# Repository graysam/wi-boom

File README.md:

# PeRci (ESP32 / ESP32-S3)

Firmware for ESP32 boards hosting a minimal web UI to safely arm and trigger a high-voltage initiator. AsyncTCP + ESPAsyncWebServer power a WebSocket control channel; configuration persists via Preferences.

## Features
- SoftAP: `PeRci-Remote` / `lollipop`, IP `10.11.12.1`.
- UI from SPIFFS (/webroot/), with first-boot Setup page to configure STA and fetch the latest UI.
- WebSocket at `/ws` for telemetry (~250 ms) and commands.
- Pulse controls: mode `single` or `buzz`, width, spacing, repeat.
- Hardware LEDs: amber/green (network/WS), red (armed), blue (pulse).
- Status bar: WS and Armed LEDs with reconnect veil; tap to show AP/STA IPs.
- OTA via ArduinoOTA (TCP/3232).
- Verbose Serial logs for boot, prefs, HTTP, WS, and actions.

## Quickstart
1. Dependencies: ESP32 core (recommended 2.0.14), libraries in `library-notes.txt`.
2. Build & Burn scripts (recommended):
   - Windows: `buildAndBurn.ps1` (or `buildAndBurn.bat` wrapper)
   - macOS/Linux: `chmod +x buildAndBurn.sh && ./buildAndBurn.sh`
   Scripts prompt for sketch, FQBN, clean, port selection, upload, and can open a serial monitor.
3. Manual (Arduino IDE):
   - ESP32 Dev Module (ESP32-WROOM-32): select Board "ESP32 Dev Module".
   - ESP32-S3 Dev Module: select Board "ESP32S3 Dev Module" and enable USB CDC on boot.
   Then open `PeRci.ino` and Upload.
4. Connect to AP `PeRci-Remote` and open `http://10.11.12.1/`.
5. OTA Update (optional):
   - Ensure your PC and the device are on the same network (AP or STA).
   - Arduino IDE: use the Network Port entry if available.
   - Arduino CLI: `arduino-cli upload -p 10.11.12.1:3232 --fqbn esp32:esp32:esp32 PeRci.ino` (replace FQBN for ESP32-S3).

## Controls & Ranges
- Mode: `single` or `buzz`.
- Width: 5-100 ms; Spacing: 10-100 ms; Repeat: 1-4.
- Arm/Disarm gates firing; cfg changes are ignored while armed.

## Build & Tools
- Scripts: see above. CLI fallback in `README.build.md`.
- Serial monitor: `arduino-cli monitor -p COMX -c baudrate=115200`.
- WebSocket test (PowerShell): `powershell -ExecutionPolicy Bypass -File tools\\test_ws.ps1`

## API Reference
See `docs/WS_API.md` for WebSocket message formats, examples, and flows.

## Code Map
- `PeRci.ino`: setup/loop, telemetry tick, indicators.
- `web_server.cpp/.h`: AP setup, async server, WebSocket, inline UI, actions.
- `config.h`: pins, SoftAP settings, defaults; edit pins here if needed.

## Hardware
- KiCad project resides in `hardware_kicad/` (schematics `*.kicad_sch`, board `*.kicad_pcb`).
- Generated artifacts (plots, fabrication outputs, iBOM) are currently included from prototyping; going forward we'll prefer attaching these to GitHub releases rather than committing bulk outputs.
- For fabrication, open in KiCad 7/8 and regenerate plots/GERBER/Drill files as needed. Additional notes may be present in `hardware_kicad/`.

## Safety
Change the default SoftAP password before field use. Treat the trigger output as live hardware; validate with a dummy load first.

## Release v1.21a
- Prototype hardware integrated and tested with the firmware.
- Repo/docs tidy-up; encoding fixes and clearer setup notes.
- Tag: `v1.21a` marks the working prototype snapshot.

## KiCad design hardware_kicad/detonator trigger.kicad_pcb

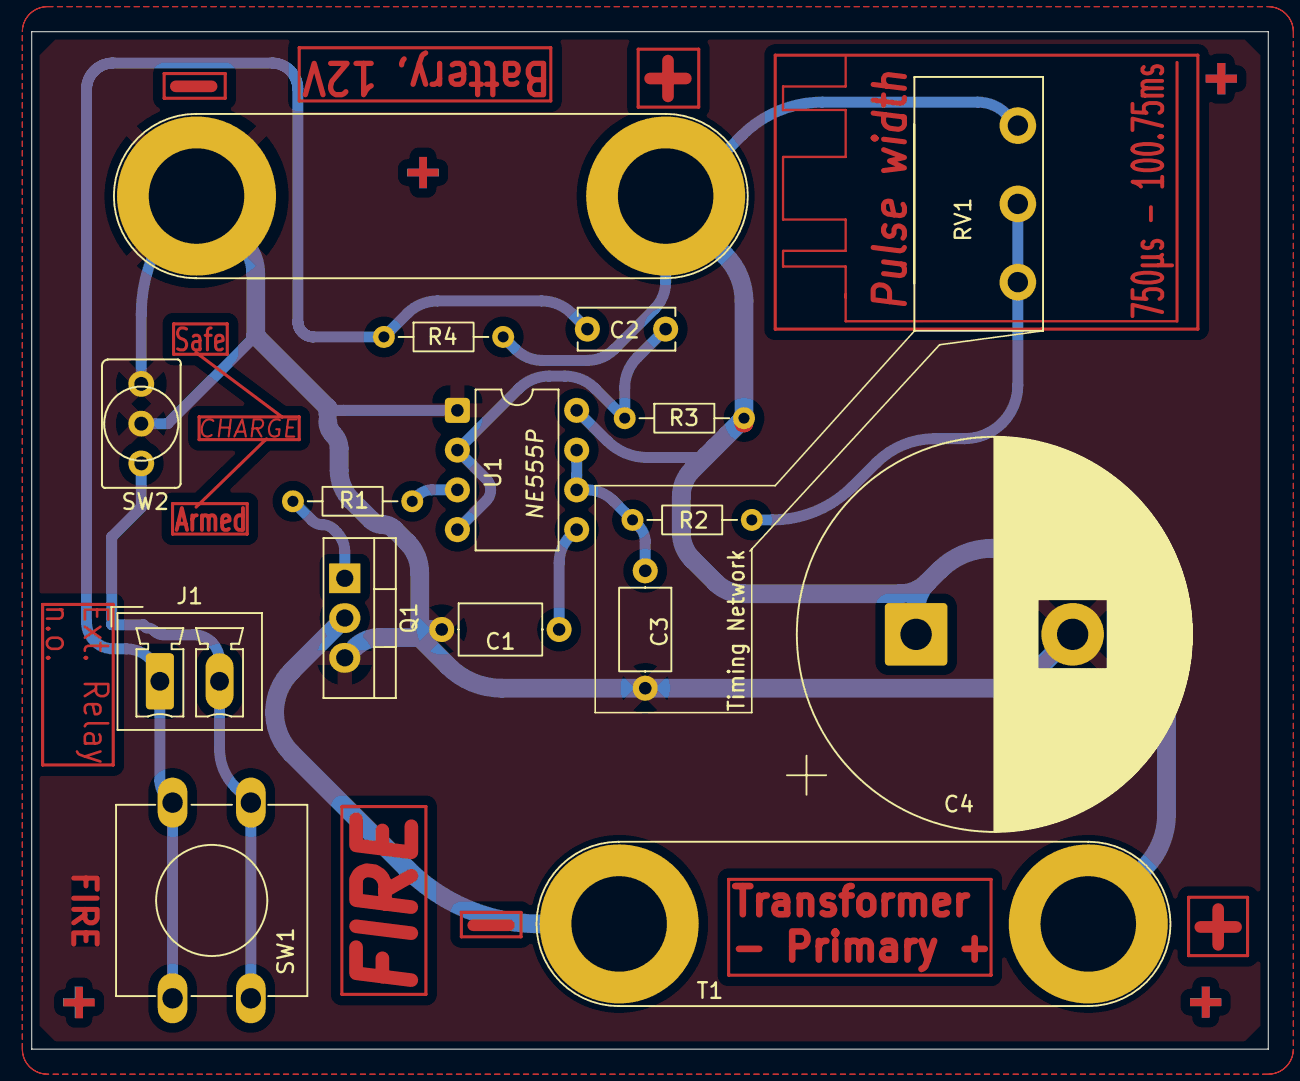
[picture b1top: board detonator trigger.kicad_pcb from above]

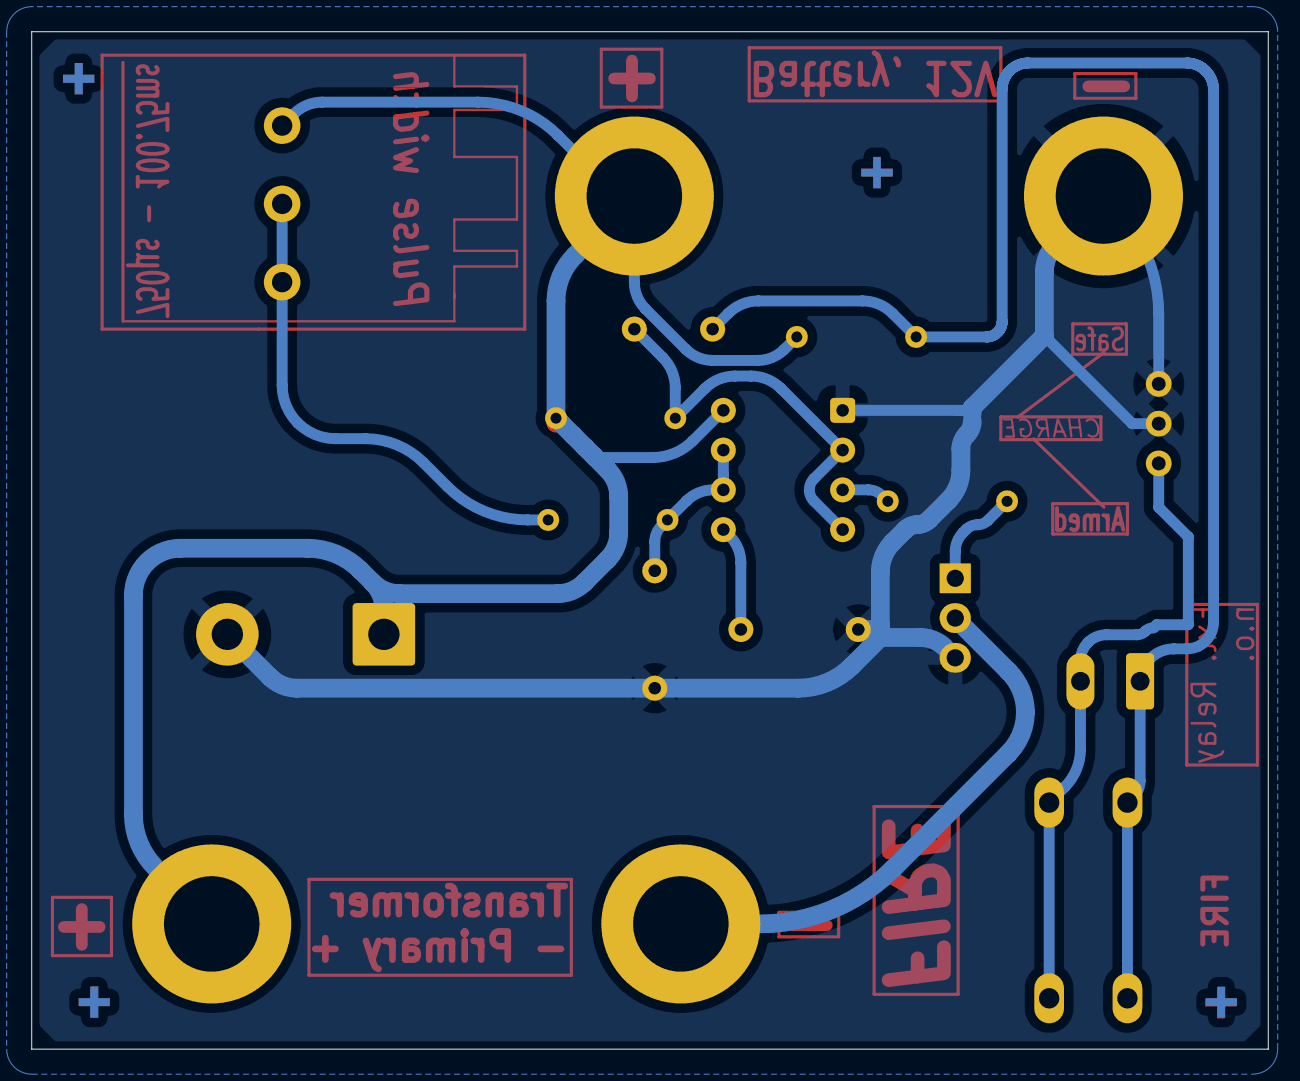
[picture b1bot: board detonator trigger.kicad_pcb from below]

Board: 2 copper layers, 79.0 x 65.0 mm, 24 parts (4 on the bottom side), 11 nets.

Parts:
C1: 100p; C_Axial_L5.1mm_D3.1mm_P7.50mm_Horizontal
C2: 10n; C_Disc_D6.0mm_W2.5mm_P5.00mm
C3: 100n; C_Axial_L5.1mm_D3.1mm_P7.50mm_Horizontal
C4: 10000uF, 40V; CP_Radial_D25.0mm_P10.00mm_SnapIn
J1: Relay_Fire; PhoenixContact_MCV_1,5_2-G-3.81_1x02_P3.81mm_Vertical
J3: + Battery (5-15V) -; Banana_Jack_2Pin
Q1: IRLI530N; TO-220-3_Vertical
R1: 100; R_Axial_DIN0204_L3.6mm_D1.6mm_P7.62mm_Horizontal
R2: 7.5k; R_Axial_DIN0204_L3.6mm_D1.6mm_P7.62mm_Horizontal
R3, R4: 100k; R_Axial_DIN0204_L3.6mm_D1.6mm_P7.62mm_Horizontal
RV1: 1M; Potentiometer_16mm-Alpha_Bourns_Omega-Single_Horizontal
SW1: BTN_FIRE; SW_PUSH-12mm
SW2: ARM; Switch_Toggle_SPDT_SubMini
T1: Ignition Coil Xformer; Banana_Jack_2Pin
U1: NE555P; DIP-8_W7.62mm
ref3, ref3#2: Fiducial_Cross_0.5mm_Mask2mm
reg1, reg1#2, reg2, reg2#2, reg2#3, reg2#4: Fiducial_Cross_0.5mm_Mask2mm

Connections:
+BATT: C4.1, J3.1, R3.2, R4.2, RV1.1, T1.1 (AA), U1.8 (VCC)
GND: C1.1, C3.2, C4.2, J3.2, Q1.3 (S), SW2.2 (B), SW2.3, U1.1 (GND)
unnamed: C2.1, J1.1, R4.1, SW1.2
unnamed: J1.2, SW1.1, SW2.1 (A)
unnamed: Q1.2 (D), T1.2 (AB)
unnamed: Q1.1 (G), R1.2
unnamed: R2.1, RV1.2, RV1.3
unnamed: C1.2, U1.5 (CV)
unnamed: C3.1, R2.2, U1.6 (THR), U1.7 (DIS)
unnamed: R1.1, U1.3 (Q)
unnamed: C2.2, R3.1, U1.2 (TR), U1.4 (R)

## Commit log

2025-09-03 Upload my starting point....
    Not good. but beginning to define the board, anyway.
2025-09-03 Rename blink_pin.ino to wb_main.ino
    yeah, somehow kept the name from examples I was browsing. This will be the name from now..
2025-09-03 Update wb_main.ino
    various changes
2025-09-03 Delete wb_main.ino
    removed to avoid confusion
2025-09-03 Update config.h
    Version 2 from Codex after some prompting
2025-09-03 Update hv_trigger_async.ino
    second round through codex
2025-09-03 Update web_server.cpp
    second run through codex
2025-09-03 Update web_server.h
    2nd round trimming from Codex
2025-09-03 docs: refresh docs to match current codebase; add AGENTS.md contributor guide
2025-09-03 fix(web_server): remove stray trailing token causing compile error
2025-09-03 test: add PowerShell WebSocket script to exercise arm/cfg/fire and observe telemetry
2025-09-03 feat(ui,led,debug): - add bottom status bar with live telemetry - optimistic arming in UI to enable FIRE; fix arm enabling bug - solid green LED when WS connected; cleanupClients for accuracy - add v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
2025-09-03 chore(scripts): add cross-platform build+burn helpers with prompts, port selection, and retry logic
2025-09-03 docs: overhaul README; add Build & Burn usage and link; add complete WS API reference; update library notes
2025-09-03 chore(windows): switch to PowerShell build script; keep .bat as wrapper; improve FQBN handling and defaults
2025-09-03 chore(scripts): add optional serial monitor to Windows (PS) and macOS/Linux scripts; fix PS 5.1 compatibility (no ternary)
2025-09-05 Update README.md
    Addressed encoding conversion artefacts throughout text. replaced several ' â€“ '-like instances with the intended character. May have missed some.
2025-09-05 feat(esp32-cam): switch pin map, target & scripts - Update config.h pins per pin_assignments.txt (16,14,15,13,12) - Remove ADC reserved usage; keep telemetry shape - Set default FQBN to esp32:esp32:e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
2025-09-05 uploading extraneous esp support files
2025-09-05 feat(scripts,net,ota): - Add pre-action menus, scan sketches/builds, build/upload/combined modes - Port selection with busy-port retry; OTA upload option (network) - Default FQBN to esp32cam with OTA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
2025-09-06 Created PROJECT_SPEC
    File describes in absolute terms the purpose and functionality of the project, such that it could be re-implemented on any platform using just this text.
2025-09-08 feat(esp8266,scaffold): migrate to ESP8266 and scaffold project\n\n- Add hv_trigger_async_ESP8266.ino (main)\n- Modules: state, storage (EEPROM), fire_engine (non-blocking), net (SoftAP+HTTP+/ws), ot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
2025-09-08 chore(repo): remove stray embedded repo 'wi-boom-8266' and add .gitignore
2025-09-09 feat(esp8266): refine timing & networking per spec\n\n- Load persisted cfg at boot; save only on accepted updates\n- Buzz timing: low period = max(spacing, guard) for >=50ms between highs\n- Track WS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
2025-09-09 feat(ui,logs): disable Fire until armed; add WS/CFG/ARM/FIRE serial logs; display connection and armed status in UI
2025-09-09 chore(logs): add HTTP GET logging for client IP and page counter
2025-09-09 feat(esp32): add ESP32 Dev Module pin map and update docs/build scripts; keep ESP32-S3 compatibility
2025-09-10 fix(ui,csp): allow inline script and ws/wss in CSP to restore WebSocket + controls on ESP32
2025-09-10 feat(ui): resilient WS with auto-reconnect + veil; status LEDs; slider value boxes; compact status bar; show AP SSID; add wsCount/apSSID telemetry
2025-09-10 docs: add CHANGELOG; update README, WS_API, README.build; add tools/test_ws.ps1
2025-09-10 chore: ignore build/ artifacts; drop tracked esp32 build outputs
2025-09-10 fix(build): use to locate script dir in PowerShell; update CHANGELOG
2025-09-18 Major schematic revision
    Hardware schematics and PCB designs added, updated to revision 1.21a. Pin assignments changed.
2025-09-18 Tidying kicad folder for Git version tracking
    Removed extraneous files, ignore kicad_backups, ibom now included under version folder, though should remove all accumulated version trees in future commit
2025-09-18 chore(repo): tidy docs and ignores; drop node_modules and backups from tracking
    - Add HARDWARE.md and expand README
    - Fix encoding issues across docs
    - Expand .gitignore for KiCad outputs and node_modules
    - Remove tracked node_modules and KiCad backup zips
2025-09-23 feat(2.0.1): migrate UI to SPIFFS with admin + updater; add timer mode and new shot logic; rebrand to PeRci\n\n- Serve UI from /webroot on SPIFFS; add immutable /admin settings page\n- Add UI updater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
2025-09-23 chore(webroot): set actual file sizes in manifest for updater estimate
2025-09-23 feat(ui): compact responsive layout for iPhone — top aligned ARM/DISARM/FIRE squares, inline slider values, logo in statusbar, floating settings gear; trim paddings and add subtle animations
2025-09-23 chore(webroot): update manifest size for index.html after responsive UI changes
2025-09-23 feat(ui): restore functional reconnect veil; enlarge logo spanning status+message bars; ensure FIRE is true 50% square; responsive spacing with clamp(); lighten backgrounds for clearer delineation
2025-09-23 fix(http): always serve /webroot as root and fallback to Admin only when UI is missing; update Admin link to /index.html so it works after UI install without reboot
2025-09-24 Delete build directory
    builds now to be accessed via releases.
2025-09-24 feat(net): runtime STA config with persistence; seed minimal webroot on first boot to guide Wi‑Fi setup and UI fetch; add network APIs and IPs in telemetry; statusbar tap shows AP/STA IPs
2025-09-24 chore: remove temp file
2025-09-24 feat(admin): add Network (STA) page at /admin/net; link from Admin; show and configure STA at runtime with clear status + internet check
2025-09-24 fix: remove UTF-8 BOM from web_server.cpp to restore build
2025-09-24 docs: rebrand to PeRci, add Makefile (makeEspArduino), update build notes, rename sketch to perci.ino and update scripts/refs
2025-09-24 chore: remove tmp files from docs processing
2025-09-24 chore: point updater to new repo URL; docs: reflect PeRci-Remote and current entry sketch (hv_trigger_async.ino) until folder is renamed
2025-09-24 refactor: rename sketch to perci.ino; update docs and AP name; update updater URL to new repo
2025-09-24 build: rename sketch to PeRci.ino to match folder; update scripts/docs
2025-09-24 chore: normalize EOLs + docs encoding; remove UTF-8 BOM from sources
